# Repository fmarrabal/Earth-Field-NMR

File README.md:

# Earth Field NMR Spectrometer

This repository contains the complete design, schematics, PCB layout, microcontroller firmware, and computer software for an Earth Field Nuclear Magnetic Resonance (EFNMR) spectrometer. This device is designed to operate using the Earth's magnetic field, providing a cost-effective and accessible NMR solution for educational and research purposes.

## Overview

Nuclear Magnetic Resonance (NMR) is a powerful analytical technique used to study the physical, chemical, and biological properties of matter. Conventional NMR spectrometers require high magnetic fields, making them expensive and limited to specialized laboratories. The Earth Field NMR (EFNMR) spectrometer, however, utilizes the Earth's magnetic field, significantly reducing the cost and complexity of the device.

This project aims to develop an EFNMR spectrometer that can be used for educational purposes, allowing students and researchers to gain hands-on experience with NMR technology without the need for high-field NMR equipment.

## Components

The EFNMR spectrometer consists of the following main components:

1. **Polarizing Coil**
   - Generates a temporary magnetic field to polarize the sample.
   - Specifications:
     - Enamelled copper wire: 1.7 mm or 14 AWG
     - Inner diameter: 80 mm
     - Outer diameter: 90 mm
     - Height: 145 mm
     - Approximate inductance: 3.4 mH
     - Approximate resistance: 0.8 Ω

2. **Receiver Coils (Antenna)**
   - Detects the signal from the polarized sample.
   - Specifications:
     - Enamelled copper wire: 0.812 mm or 21 AWG
     - Inner diameter: 25 mm
     - Outer diameter: 40 mm
     - Height: 100 mm
     - Approximate inductance per coil: 2.56 mH
     - Approximate resistance per coil: 2.5 Ω

3. **Power Circuit**
   - Controls the power supply to the polarizing coil.
   - Utilizes a MOSFET for fast switching and high current handling.

4. **Receiver Circuit**
   - Amplifies and filters the weak NMR signal from the receiver coils.
   - Consists of a low-noise instrumentation amplifier, additional amplification stages, and a band-pass filter.

5. **Microcontroller (STM32F373)**
   - Handles control tasks, signal digitization, and communication with a computer.
   - Features a 16-bit ADC and USB communication.

6. **Computer Software**
   - Provides a user interface for configuring experiments, visualizing results, and performing signal processing.
   - Developed in C# for ease of use and rapid implementation of new features.

## Usage

To use the EFNMR spectrometer, follow these steps:

1. **Assemble the Hardware**
   - Ensure all components are correctly assembled and connected as per the provided schematics and PCB layout.

2. **Upload the Firmware**
   - Program the STM32F373 microcontroller with the provided firmware.

3. **Install the Software**
   - Install the computer software on a compatible system.

4. **Perform an Experiment**
   - Use the software to configure the experimental parameters (e.g., number of samples, number of scans, pulse time).
   - Align the coils with the Earth's magnetic field using the built-in magnetometer.
   - Start the experiment and visualize the results in the software.

## Repository Contents

- `PCB/`: PCB layout files for manufacturing the PCBs.
- `Firmware/`: Source code for the microcontroller firmware.
- `EFMNR/`: Source code and binaries for the computer software.
- `Assembly/`: CAD designs for 3D printed parts used in the spectrometer assembly.

## Acknowledgements

This project was developed at the University of Almeria, Spain. Also, The research received generous funding from the following sources:
- the State Research Agency of the Spanish Ministry of Science and Innovation (PID2021-126445OB-I00)
- the Gobierno de España MCIN/AEI/10.13039 /501100011033
- European Union “Next Generation EU”/PRTR (PDC2021-121248-I00, PLEC2021- 007774 and CPP2022-009967).

We extend our heartfelt gratitude to all the contributors who played a vital role in making this project a reality.

## Reference

Please cite this project using the following BibTeX entry:

@article{Viciana2024,
author = {Viciana, Eduardo and Mart{\'{i}}nez-Lao, Juan Antonio and L{\'{o}}pez-Lao, Emilio and Fern{\'{a}}ndez, Ignacio and Arrabal-Campos, Francisco Manuel},
doi = {10.3390/s24175537},
issn = {1424-8220},
journal = {Sensors},
keywords = {earth,efnmr,nmr spectrometer,s field nmr},
month = {aug},
number = {17},
pages = {5537},
title = {{Development of an Earth-Field Nuclear Magnetic Resonance Spectrometer: Paving the Way for AI-Enhanced Low-Field Nuclear Magnetic Resonance Technology}},
url = {https://www.mdpi.com/1424-8220/24/17/5537},
volume = {24},
year = {2024}
}

## Contact

For questions or further information, please contact fmarrabal@ual.es

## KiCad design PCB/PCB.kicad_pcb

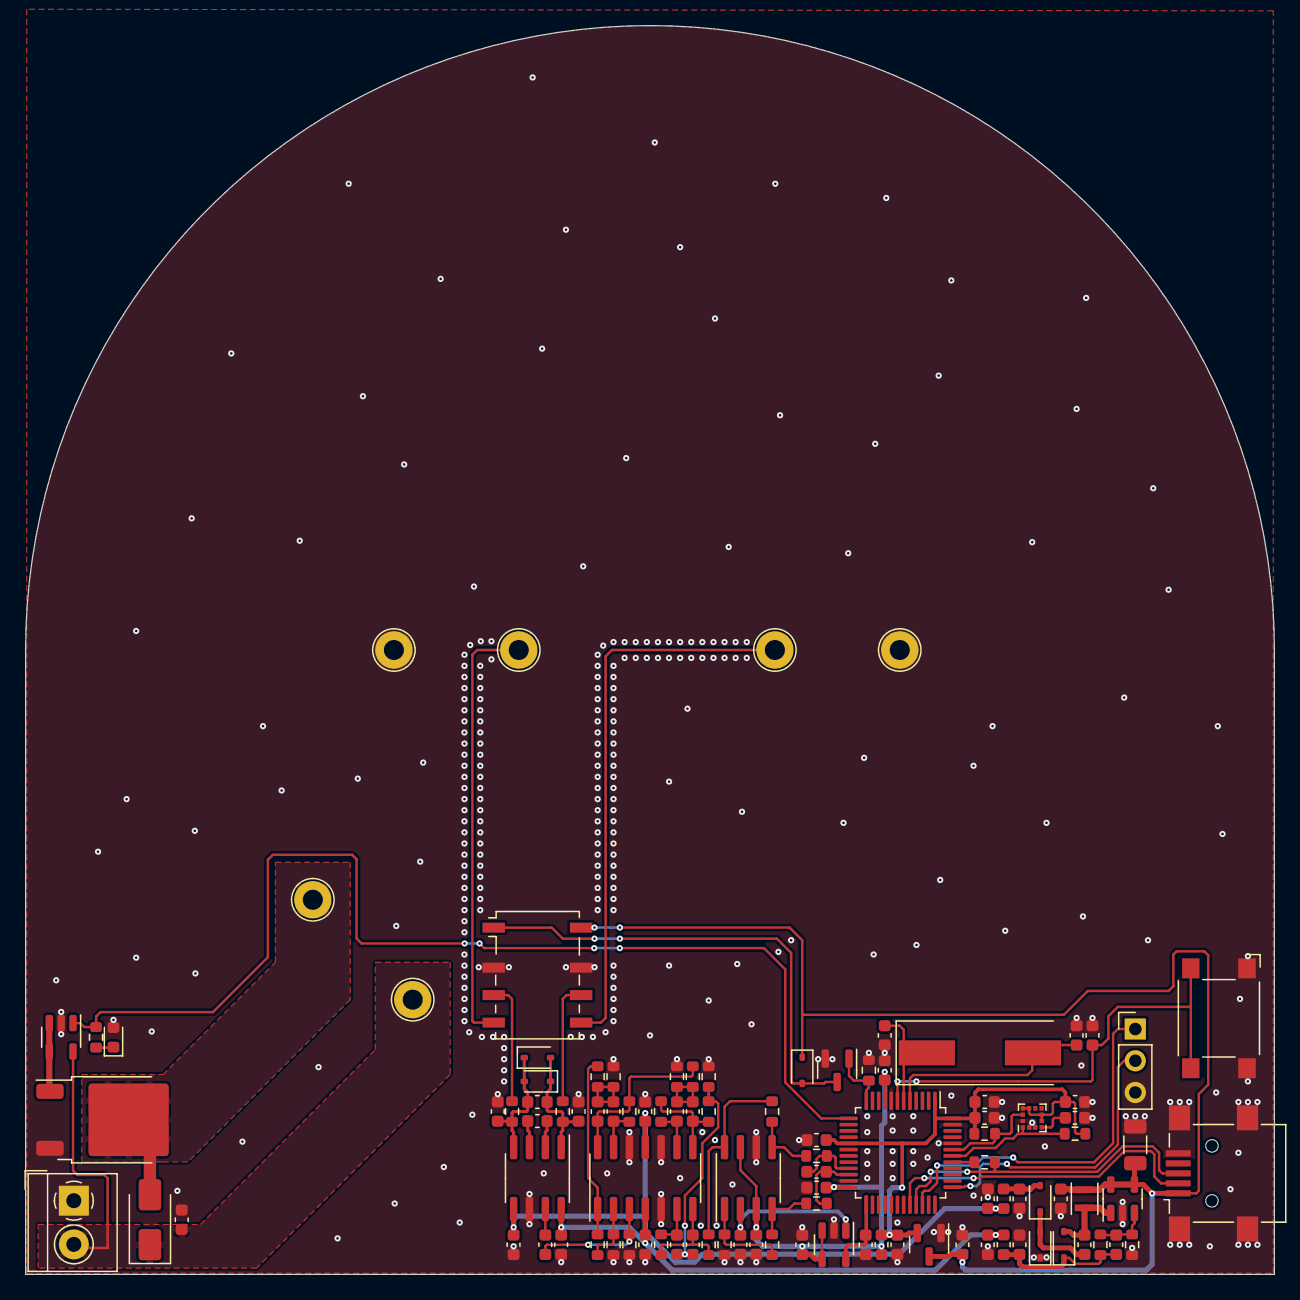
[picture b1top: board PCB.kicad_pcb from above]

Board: 2 copper layers, 100.0 x 100.0 mm, 103 parts (0 on the bottom side), 58 nets.

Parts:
C1: 100uF; C_1206_3216Metric
C2, C3, C4, C6, C7, C8, C11, C12, C13, C19, C25, C38, C39: 100nF; C_0603_1608Metric
C5, C15, C16, C23, C24: 1uF; C_0603_1608Metric
C9, C10: 12pF; C_0603_1608Metric
C14: 120pF; C_0603_1608Metric
C17, C18, C26, C27, C28, C29, C30, C31, C32, C33, C34, C40: C_Small; C_0603_1608Metric
C20, C21: 10nF; C_0603_1608Metric
C22: 220pF; C_0603_1608Metric
C35, C36, C37, C41: CC0603KRX7R9BB104; C_0603_1608Metric
D1: SMAJ45A; D_SMA
D2: LED; LED_0603_1608Metric
D3, D4, D5: SD103AWS-7-F; D_SOD-323
D6, D7: SD101A; D_SOD-323
D8: 1.5KExxA; D_SOD-323
FB1, FB2, FB3: FerriteBead_Small; L_0603_1608Metric
J1: USB_B_Mini; USB_Mini-B_Lumberg_2486_01_Horizontal
J2: Screw_Terminal_01x02; TerminalBlock_4Ucon_1x02_P3.50mm_Horizontal
J3: Conn_01x03; PinHeader_1x03_P2.54mm_Vertical
K1: G6K-2; Relay_DPDT_Omron_G6K-2F-Y
L1: CBC3225T100KR; L_Murata_DFE201610P
Q1: IPD50R3K0CE; TO-252-2
Q2: 2N7002; SOT-23
R1: 1k5; R_0603_1608Metric
R2, R3: 4k7; R_0603_1608Metric
R4, R6, R11, R12, R13, R14, R15, R16, R17, R18, R19, R20, R21, R22, R23, R24, R25, R26, R28: R_Small; R_0603_1608Metric
R7: 15k; R_0603_1608Metric
R8: 150k; R_0603_1608Metric
R9, R10: 49.9h; R_0603_1608Metric
R27: R_0603_1608Metric
SW1: SW_Omron_B3FS; SW_SPST_Omron_B3FS-100xP
TP1, TP2, TP3, TP4, TP5, TP6: TestPoint; TestPoint_Loop_D2.60mm_Drill1.6mm_Beaded
U1: STM32F373C8Tx; LQFP-48_7x7mm_P0.5mm
U2: LIS3MDL; LGA-12_2x2mm_P0.5mm
U3: INA848; SOIC-8_3.9x4.9mm_P1.27mm
U4: LM27313XMFX/NOPB; SOT-23-5
U5: OPA4189xD; SOIC-14_3.9x8.7mm_P1.27mm
U6: THS4561; SOIC-8_3.9x4.9mm_P1.27mm
U7: UCC44273; SOT-23-5
U8: REF2025AIDDCR; SOT-23-5
U9: MCP1700-3.3; SOT-23
Y1: 8MHz; Crystal_SMD_HC49-SD

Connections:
1.25V_{REF}: C36.1, U6.2 (V_{OCM}), U8.1 (Vbias)
2.5V_{REF}: C35.2, U1.25 (VREFSD+), U8.5 (Vref)
3.3V: C2.2, C3.1, C5.1, C6.1, C38.2, FB1.1, R2.1, R3.1, U1.1 (VBAT), U1.17 (VDD), U1.48 (VDD), U2.5 (Vdd), U2.6 (Vdd_IO), U2.9 (SDO/SA1), U2.10 (~CS), U9.2 (VOUT)
3.3V_{A}: C4.1, C7.1, C34.1, C37.2, FB1.2, U1.9 (VDDA), U1.24 (VDDSD), U6.3 (V_{S+}), U6.7 (~PD), U8.3 (EN), U8.4 (VIN)
5V: C1.1, C12.1, C39.2, D8.1 (A1), J1.1 (VBUS), K1.8, L1.1, U4.4 (EN), U4.5 (VIN), U9.3 (VIN)
12V: C17.1, C23.1, C33.1, FB2.2, U3.8 (Vs+), U5.4 (V+)
-12V: C18.1, C24.2, C32.1, FB3.2, U3.5 (Vs-), U5.11 (V-)
ADC+: R24.2, R27.1, U6.5
ADC-: R25.2, R28.1, U6.4
EN_{B}: R6.1, U1.13 (PA3), U7.1 (IN)
EN_{Relay}: Q2.1 (G), R4.1, U1.12 (PA2)
GNDD: C1.2, C2.1, C3.2, C4.2, C5.2, C6.2, C7.2, C8.2, C9.1, C10.1, C11.2, C12.2, C15.2, C16.1, C17.2, C18.2, C20.1, C21.2, C23.2, C24.1, C32.2, C33.2, C34.2, C35.1, C36.2, C37.1, C38.1, C39.1, C41.2, D2.2 (A), D4.1 (K), J1.5 (GND), J1.6 (Shield), J2.1, J3.3, K1.2, K1.7, Q1.3 (S), Q2.2 (S), R4.2, R7.2, R11.2, R12.2, R16.1, R18.1, R21.1, R26.1, SW1.1, TP2.1, TP6.1, U1.8 (VSSA), U1.23 (VSSSD), U1.44 (BOOT0), U1.47 (VSS), U2.2 (GND), U2.3 (GND), U2.12 (GND), U3.6 (Ref), U4.2 (GND), U5.5 (+), U5.10 (+), U5.12 (+), U6.6 (V_{S-}), U7.2 (GND), U8.2 (GND), U9.1 (GND)
unnamed: C22.1, U3.2 (Rg)
unnamed: C22.2, U3.3 (Rg)
unnamed: C25.1, U3.7
unnamed: C26.1, C27.1, R14.2, R16.2
unnamed: C27.2, R15.2, R17.1, U5.14
unnamed: C28.1, C29.1, R17.2, R18.2
unnamed: C28.2, R19.2, R20.1, U5.8
unnamed: C30.1, C31.1, R20.2, R21.2
unnamed: C30.2, R22.2, R23.1, U5.7
unnamed: C41.1, D1.1 (A1), J2.2, TP4.1, U7.5 (Vdd)
unnamed: D1.2 (A2), Q1.2 (D), TP5.1
unnamed: D2.1 (K), R6.2
unnamed: C13.1, D3.2 (A), L1.2, U4.1 (SW)
unnamed: C14.1, C15.1, D3.1 (K), FB2.1, R8.1
unnamed: C13.2, D4.2 (A), D5.1 (K)
unnamed: C16.2, D5.2 (A), FB3.1
unnamed: C19.2, C21.1, D6.2 (A), D7.1 (A1), R10.1, U3.4 (+)
unnamed: C19.1, C20.2, D6.1 (K), D7.2 (A2), R9.1, U3.1 (-)
unnamed: D8.2 (A2), K1.1, Q2.3 (D)
unnamed: J1.3 (D+), R1.2, U1.33 (PA12)
unnamed: J1.2 (D-), U1.32 (PA11)
unnamed: J3.1, U1.34 (PA13)
unnamed: J3.2, U1.37 (PA14)
unnamed: K1.3, R10.2
unnamed: K1.4, TP3.1
unnamed: K1.5, TP1.1
unnamed: K1.6, R9.2
unnamed: Q1.1 (G), U7.3 (OUT), U7.4 (OUT)
unnamed: R13.2, R14.1, U5.1
unnamed: C8.1, SW1.2, U1.7 (NRST)
unnamed: R1.1, U1.41 (PB5)
unnamed: C40.1, R27.2, U1.21 (PE8)
unnamed: C40.2, R28.2, U1.22 (PE9)
unnamed: C9.2, U1.5 (PF0), Y1.2
unnamed: C10.2, U1.6 (PF1), Y1.1
unnamed: C11.1, U2.4 (C1)
unnamed: C14.2, R7.1, R8.2, U4.3 (FB)
unnamed: C25.2, R11.1, U5.3 (+)
unnamed: R12.1, R13.1, U5.2 (-)
unnamed: C31.2, R22.1, U5.6 (-)
unnamed: C29.2, R19.1, U5.9 (-)
unnamed: C26.2, R15.1, U5.13 (-)
unnamed: R23.2, R24.1, U6.8 (+)
unnamed: R25.1, R26.2, U6.1 (-)
SCL: R2.2, U1.42 (PB6), U2.1 (SCL/SPC)
SDA: R3.2, U1.43 (PB7), U2.11 (SDA/SDI/SDO)

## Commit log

2024-03-26 PRIMERA SUBIDA DE ARCHIVOS
    Este código es el que se ha programado para el TFG de Emilio
2024-04-14 Añadido el PCB y Firmware. El PCB va, aunque tengo que meter una pista que falta que ahora esta con un cable. El firmware se conecta al PC, pero no hace lo que deberia de momento por que es de otro p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
2024-07-15 Firmware updated
2024-07-18 Actualizado software PC
